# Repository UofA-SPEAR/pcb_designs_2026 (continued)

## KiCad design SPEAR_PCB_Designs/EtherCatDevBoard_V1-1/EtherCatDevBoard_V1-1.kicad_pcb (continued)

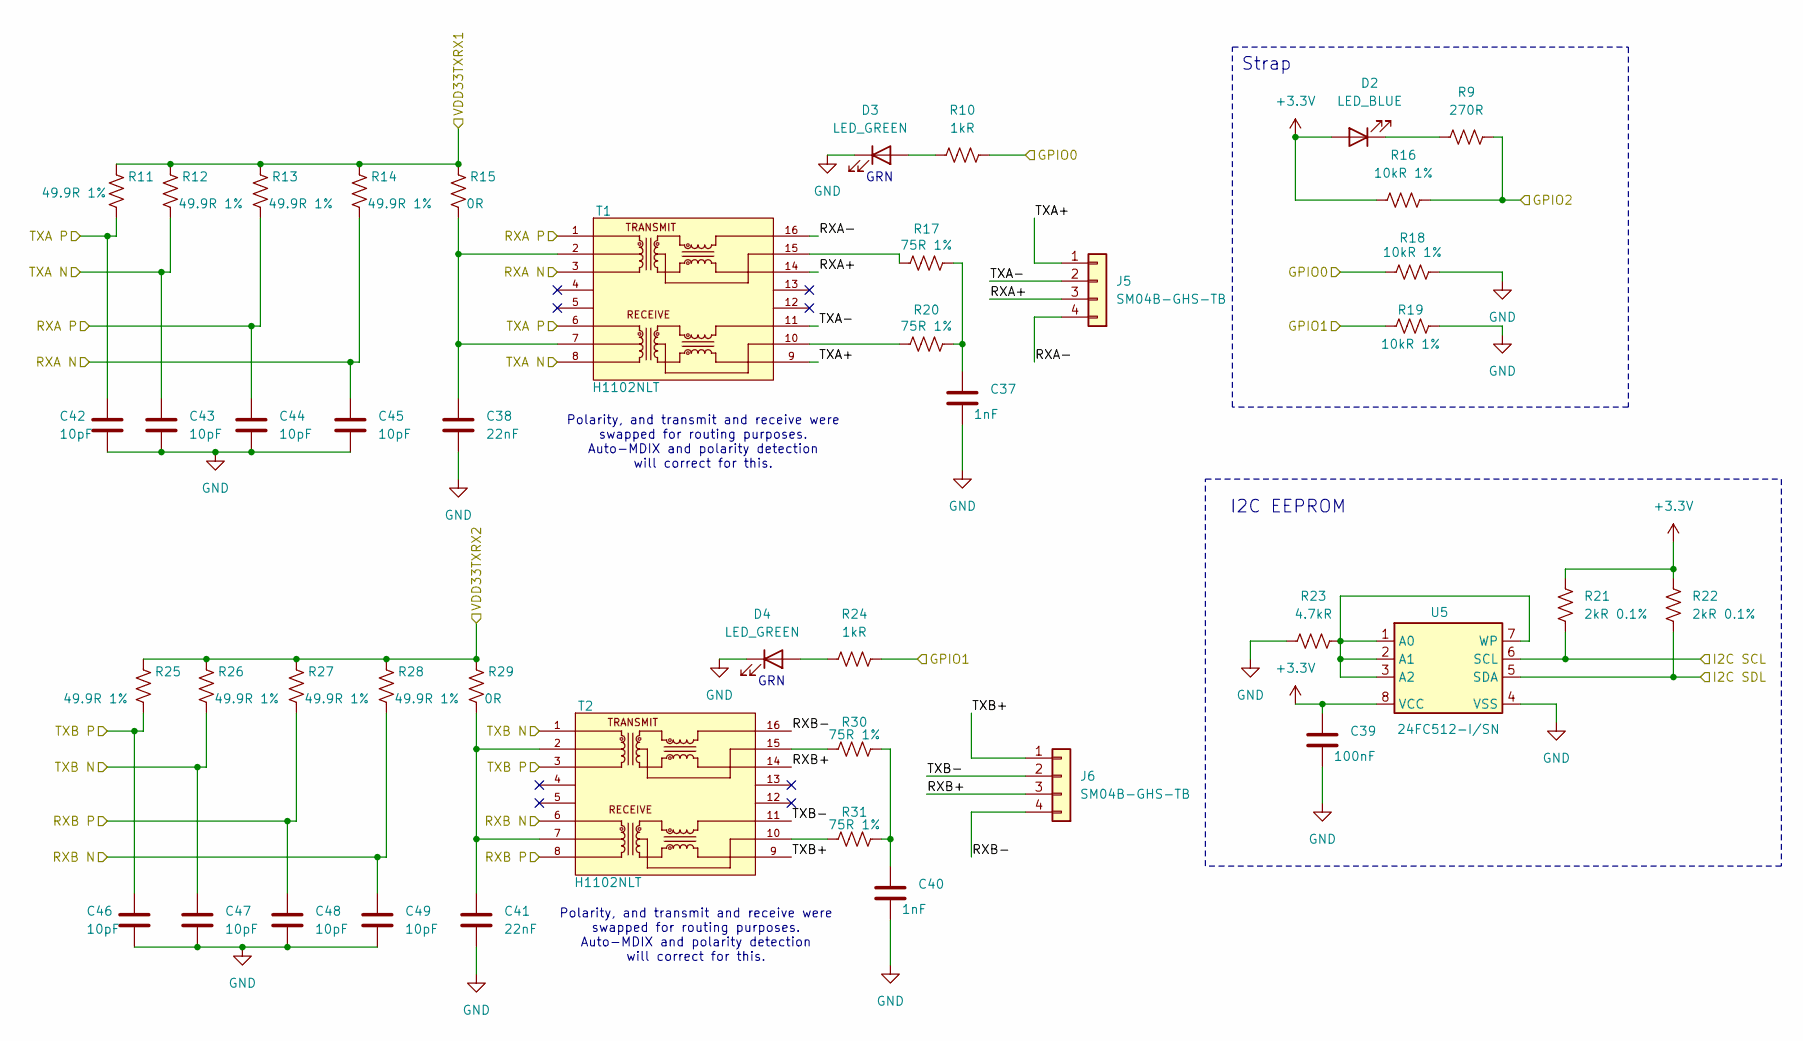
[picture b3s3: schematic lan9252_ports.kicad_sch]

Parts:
C37, C40: 1nF; C_0402_1005Metric; DigiKey_Part_Number 1276-1032-1-ND
C38, C41: 22nF; C_0402_1005Metric; DigiKey_Part_Number 1276-1537-1-ND
C39: 100nF; C_0402_1005Metric; DigiKey_Part_Number 1276-1043-1-ND
C42, C43, C44, C45, C46, C47, C48, C49: 10pF; C_0402_1005Metric; DigiKey_Part_Number 1276-1139-1-ND
D2: LED_BLUE; LED_0603_1608Metric; DigiKey_Part_Number 732-12013-1-ND
D3, D4: LED_GREEN; LED_0603_1608Metric; DigiKey_Part_Number 732-12017-1-ND
J5, J6: SM04B-GHS-TB; JST_GH_SM04B-GHS-TB_1x04-1MP_P1.25mm_Horizontal; DigiKey_Part_Number 455-1566-1-ND
R9: 270R; R_0402_1005Metric; DigiKey_Part_Number 311-270LRCT-ND
R10, R24: 1kR; R_0402_1005Metric; DigiKey_Part_Number 311-1.0KJRCT-ND
R11, R12, R13, R14, R25, R26, R27, R28: 49.9R 1%; R_0402_1005Metric; DigiKey_Part_Number 311-49.9LRCT-ND
R15, R29: 0R; R_0402_1005Metric; DigiKey_Part_Number 311-0.0JRCT-ND
R16, R18, R19: 10kR 1%; R_0402_1005Metric; DigiKey_Part_Number 311-10.0KLRCT-ND
R17, R20, R30, R31: 75R 1%; R_0402_1005Metric; DigiKey_Part_Number 13-RC0402FR-1375RLCT-ND
R21, R22: 2kR 0.1%; R_0402_1005Metric; DigiKey_Part_Number YAG2303CT-ND
R23: 4.7kR; R_0402_1005Metric; DigiKey_Part_Number 311-4.7KJRCT-ND
T1, T2: H1102NLT; XFMR_H1102NLT; PARTREV NA; DigiKey_Part_Number 553-1532-1-ND
U5: 24FC512-I/SN; SOIC-8_3.9x4.9mm_P1.27mm; DigiKey_Part_Number 24FC512-I/SN-ND

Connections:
+3.3V: C39.1, D2.2 (A), R16.2, R21.1, R22.1, U5.8 (VCC); also elsewhere on the board
/LAN9252/GPIO0: R10.1, R18.2; also elsewhere on the board
/LAN9252/GPIO1: R19.2, R24.1; also elsewhere on the board
/LAN9252/GPIO2: R9.1, R16.1; also elsewhere on the board
/LAN9252/I2C_SCL: R21.2, U5.6 (SCL); also elsewhere on the board
/LAN9252/I2C_SDL: R22.2, U5.5 (SDA); also elsewhere on the board
/LAN9252/LAN9252 Ports/RXA+: J5.3, T1.14
/LAN9252/LAN9252 Ports/RXA-: J5.4, T1.16
/LAN9252/LAN9252 Ports/RXB+: J6.3, T2.14
/LAN9252/LAN9252 Ports/RXB-: J6.4, T2.16
/LAN9252/LAN9252 Ports/TXA+: J5.1, T1.9
/LAN9252/LAN9252 Ports/TXA-: J5.2, T1.11
/LAN9252/LAN9252 Ports/TXB+: J6.1, T2.9
/LAN9252/LAN9252 Ports/TXB-: J6.2, T2.11
/LAN9252/RXA_N: C45.1, R14.2, T1.3; also elsewhere on the board
/LAN9252/RXA_P: C44.1, R13.2, T1.1; also elsewhere on the board
/LAN9252/RXB_N: C49.1, R28.2, T2.6; also elsewhere on the board
/LAN9252/RXB_P: C48.1, R27.2, T2.8; also elsewhere on the board
/LAN9252/TXA_N: C43.1, R12.2, T1.8; also elsewhere on the board
/LAN9252/TXA_P: C42.1, R11.2, T1.6; also elsewhere on the board
/LAN9252/TXB_N: C47.1, R26.2, T2.1; also elsewhere on the board
/LAN9252/TXB_P: C46.1, R25.2, T2.3; also elsewhere on the board
/LAN9252/VDD33TXRX1: R11.1, R12.1, R13.1, R14.1, R15.1; also elsewhere on the board
/LAN9252/VDD33TXRX2: R25.1, R26.1, R27.1, R28.1, R29.1; also elsewhere on the board
GND: C37.2, C38.2, C39.2, C40.2, C41.2, C42.2, C43.2, C44.2, C45.2, C46.2, C47.2, C48.2, C49.2, D3.1 (K), D4.1 (K), R18.1, R19.1, R23.1, U5.4 (VSS); also elsewhere on the board
unnamed: C37.1, R17.2, R20.2
unnamed: C38.1, R15.2, T1.2, T1.7
unnamed: C40.1, R30.2, R31.2
unnamed: C41.1, R29.2, T2.2, T2.7
unnamed: D2.1 (K), R9.2
unnamed: D3.2 (A), R10.2
unnamed: D4.2 (A), R24.2
unnamed: R17.1, T1.15
unnamed: R20.1, T1.10
unnamed: R30.1, T2.15
unnamed: R31.1, T2.10
unnamed: R23.2, U5.1 (A0), U5.2 (A1), U5.3 (A2), U5.7 (WP)

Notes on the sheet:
Polarity, and transmit and receive were swapped for routing purposes. Auto-MDIX and polarity detection will correct for this.
GRN
Strap
I2C EEPROM

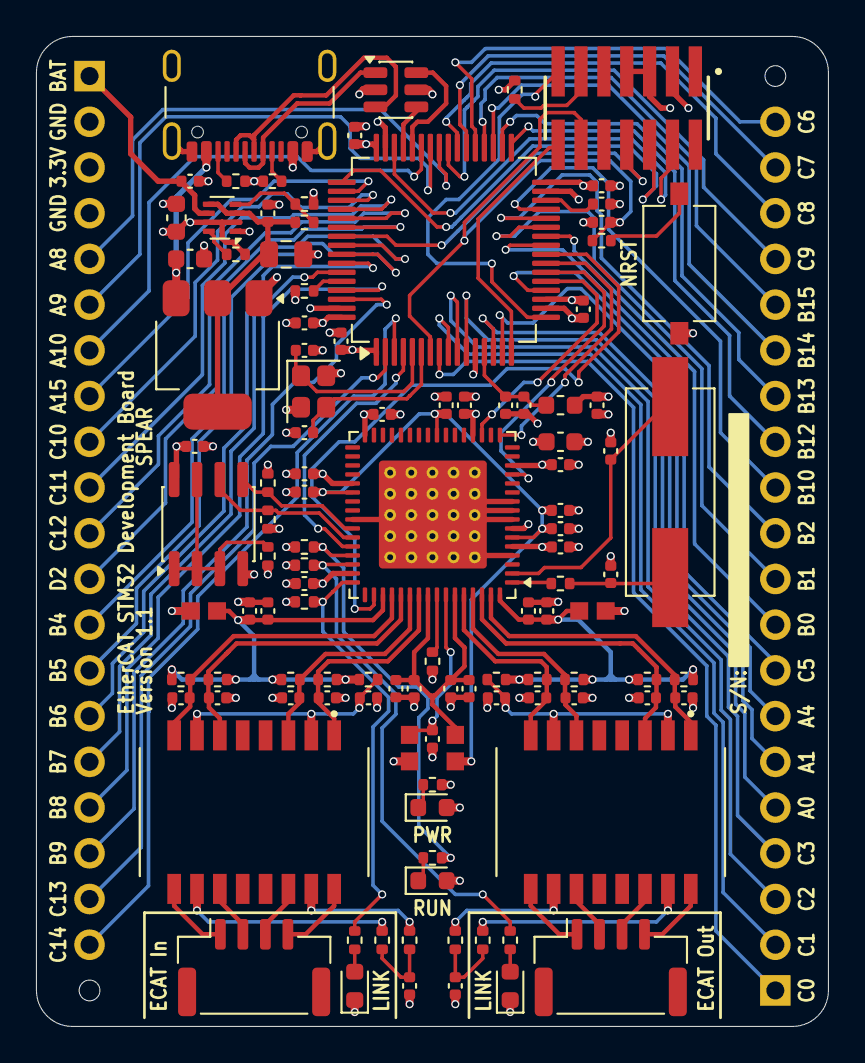
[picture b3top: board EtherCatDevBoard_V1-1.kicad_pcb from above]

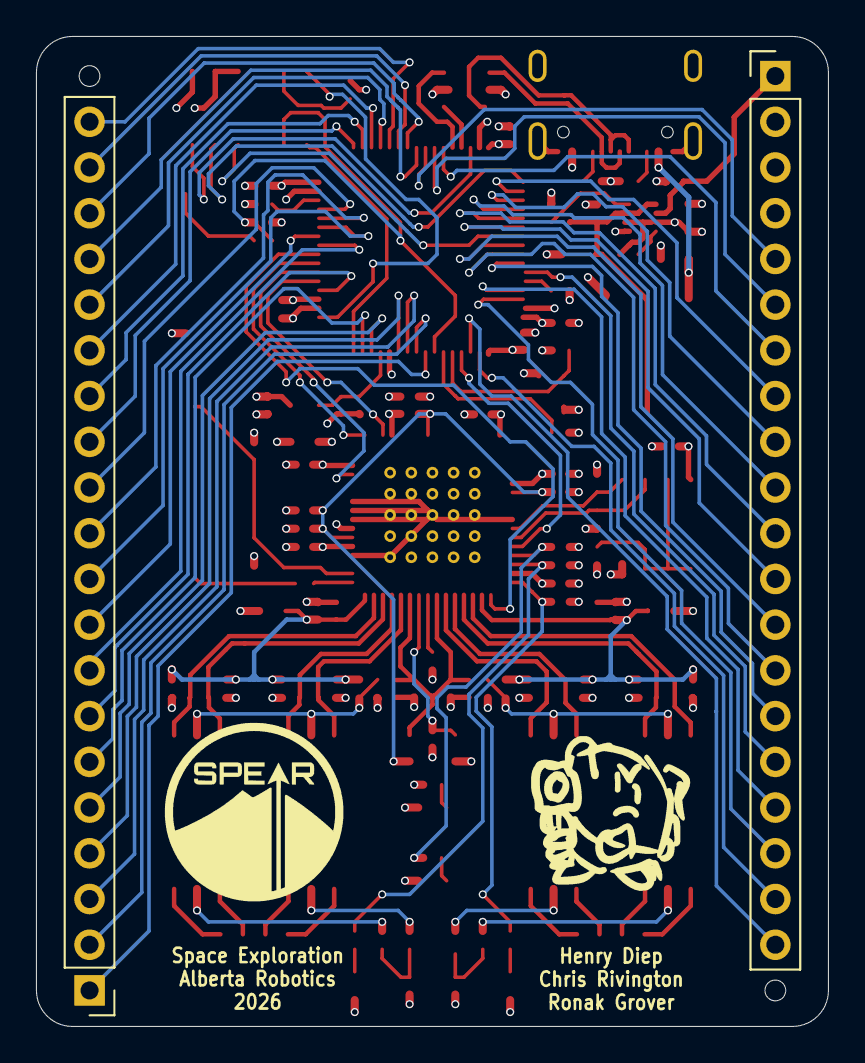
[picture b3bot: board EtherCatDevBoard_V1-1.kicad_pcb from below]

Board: 4 copper layers, 44.0 x 55.0 mm, 112 parts (2 on the bottom side), 110 nets.

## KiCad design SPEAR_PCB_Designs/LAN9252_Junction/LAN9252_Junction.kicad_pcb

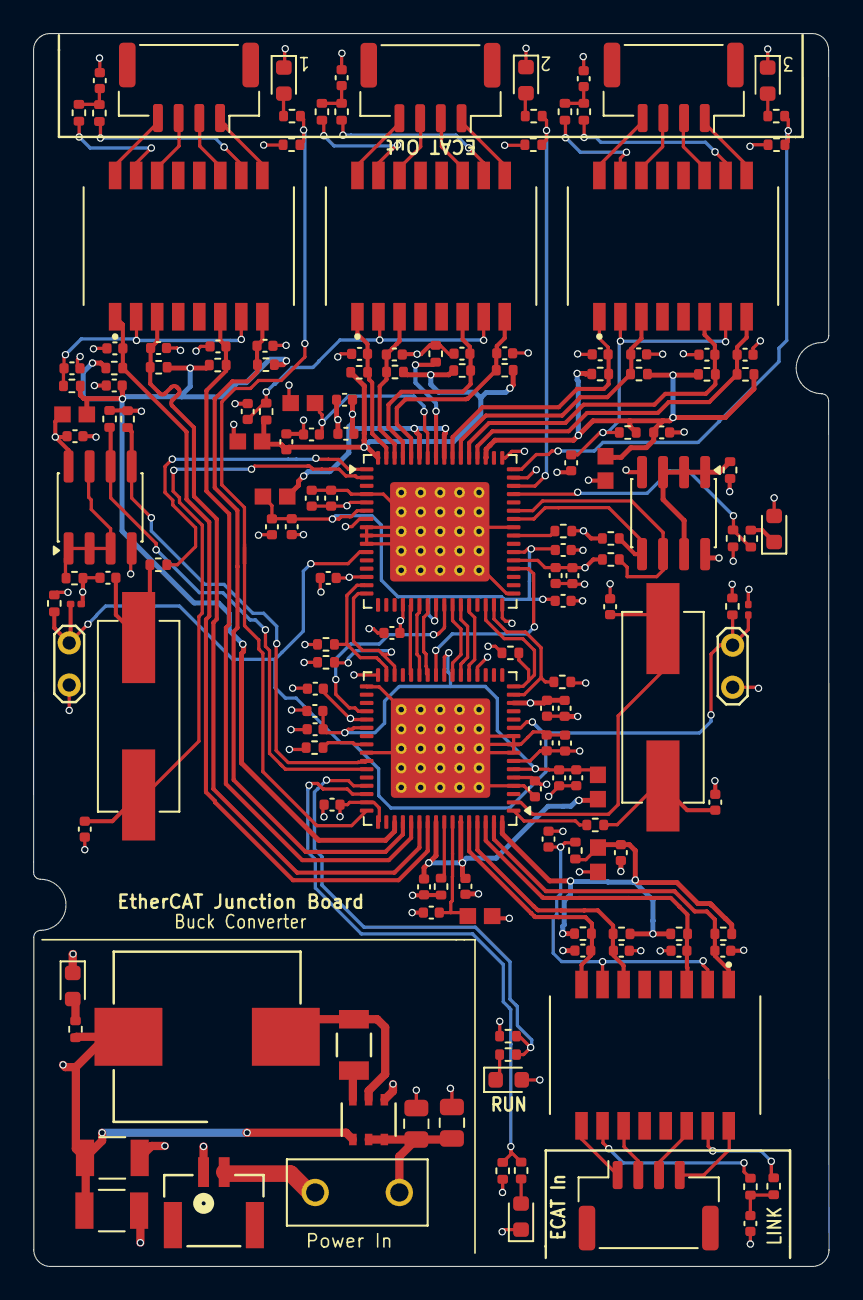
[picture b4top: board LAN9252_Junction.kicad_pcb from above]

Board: 4 copper layers, 48.0 x 74.4 mm, 161 parts (0 on the bottom side), 106 nets.

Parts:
C1, C4, C31, C34: 18pF; C_0402_1005Metric
C2, C3, C5, C6, C8, C9, C11, C12, C13, C14, C15, C16, C17, C32, C33, C35, C36, C38, C39, C41, C42, C43, C44, C45, C46, C47: 0.1uF; C_0402_1005Metric
C7, C37: 1uF; C_0402_1005Metric
C10, C40: 470 pF; C_0402_1005Metric
C18, C19, C20, C21, C22, C23, C24, C25, C48, C49, C50, C51, C52, C53, C54, C55: 10p; C_0402_1005Metric
C26, C27, C56, C57: 22n; C_0402_1005Metric
C28, C29, C58, C59: 1000 pF; C_0402_1005Metric
C30, C60: 0.1 uF; C_0402_1005Metric
C61, C62: 10uF; C_0805_2012Metric
C63: 150nF; CAP_CC1206_YAG
C64, C65: 22uF; CAP_C3225X7R1C226M250AC
C66, C67: 0.1uF; C_0201_0603Metric
D1, D2, D3, D4, D5, D6, D7: LED; LED_0603_1608Metric
F3: 2A; FUSE_36912000440
FB1, FB3, FB4, FB5, FB7, FB8: BLM18EG221SN1D; Ferrite_bead
FB2, FB6: FerriteBead; Ferrite_bead
J1, J2, J3, J4: SM04B-GHS-TB; JST_GH_SM04B-GHS-TB_1x04-1MP_P1.25mm_Horizontal
J5: SM02B-GHS-TB; CONN_SM02B-GHS_JST
J8, J9: Conn_01x02_Pin; TestPoint_2Pads_Pitch2.54mm_Drill0.8mm
L1: 3.9uH; L_Wurth_WE-LHMI-1040_L1
R1, R2: 4K7; R_0402_1005Metric
R3, R15, R16, R30, R42, R43: 0R; R_0402_1005Metric
R4, R31: 12.1k; R_0402_1005Metric
R5, R6, R32, R33: 141 R; R_0402_1005Metric
R7, R8, R9, R10, R11, R12, R13, R14, R34, R35, R36, R37, R38, R39, R40, R41: 49.9R 1%; R_0402_1005Metric
R17, R22, R44, R49, R59: 1k; R_0402_1005Metric
R18, R19, R20, R21, R45, R46, R47, R48: 75R 1%; R_0402_1005Metric
R23, R50: 4.7kR; R_0402_1005Metric
R24, R25, R26, R51, R52, R53: 10kR; R_0402_1005Metric
R27, R54: 270R; R_0402_1005Metric
R28, R29, R55, R56: 2kR; R_0402_1005Metric
R57, R58: 10k; R_0402_1005Metric
T1, T2, T3, T4: H1102NLT; XFMR_H1102NLT
U1, U3: LAN9252_ML; LAN9252_QFN UPDATED
U2, U4: 24FC512; SOIC-8_3.9x4.9mm_P1.27mm
U5: AP63203WU; AP63203WU-7_DIO-L
Y1, Y2: 25MHz; Y_Wurth_WE-XTAL_Quartz-HC49-4HSMX

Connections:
+3.3V: C11.1, C13.1, C14.1, C15.1, C16.1, C17.1, C30.1, C41.1, C43.1, C44.1, C45.1, C46.1, C47.1, C60.1, C64.1, C65.1, D3.2 (A), D6.2 (A), FB1.1, FB2.1, FB3.2, FB5.1, FB6.1, FB7.2, L1.2, R1.2, R2.2, R24.2, R26.1, R28.1, R29.1, R51.2, R52.1, R53.1, R55.1, R56.1, R57.1, R58.1, R59.1, U1.5 (VDD33), U1.7 (REG_EN), U1.14 (VDDIO), U1.20 (VDDIO__1), U1.32 (VDDIO__2), U1.37 (VDDIO__3), U1.47 (VDDIO__4), U1.49 (D4/GPI3/GPO3), U2.8 (VCC), U3.5 (VDD33), U3.7 (REG_EN), U3.14 (VDDIO), U3.20 (VDDIO__1), U3.32 (VDDIO__2), U3.37 (VDDIO__3), U3.47 (VDDIO__4), U3.49 (D4/GPI3/GPO3), U4.8 (VCC), U5.1 (FB)
/Buck Converter/BST: C63.2, U5.6 (BST)
/Buck Converter/BUCK_PWR: C61.1, C62.1, F3.1, U5.2 (EN), U5.3 (IN)
/Buck Converter/SW: C63.1, L1.1, U5.5 (SW)
/LAN9252 System 1/GPIO0: R22.1, R25.2, U1.48 (LINKACTLED0/TDO/~CHIP_MODE0)
/LAN9252 System 1/GPIO1: R17.1, R26.2, U1.46 (LINKACTLED1/TDI/~CHIP_MODE1)
/LAN9252 System 1/GPIO2: R24.1, R27.1, U1.45 (RUNLED/~E2PSIZE)
/LAN9252 System 1/I2C_SCL: R28.2, U1.43 (EESCL/TCK), U2.6 (SCL)
/LAN9252 System 1/I2C_SDL: R29.2, U1.42 (EESDA/TMS), U2.5 (SDA)
/LAN9252 System 1/LAN9252 Ports/RXA+: J2.3, T2.14
/LAN9252 System 1/LAN9252 Ports/RXA-: J2.4, T2.16
/LAN9252 System 1/LAN9252 Ports/RXB+: J1.3, T1.14
/LAN9252 System 1/LAN9252 Ports/RXB-: J1.4, T1.16
/LAN9252 System 1/LAN9252 Ports/TXA+: J2.1, T2.9
/LAN9252 System 1/LAN9252 Ports/TXA-: J2.2, T2.11
/LAN9252 System 1/LAN9252 Ports/TXB+: J1.1, T1.9
/LAN9252 System 1/LAN9252 Ports/TXB-: J1.2, T1.11
/LAN9252 System 1/MII_CLK25: U1.25 (A1/ALELO), U3.36 (D6/GPI0/GPO0)
/LAN9252 System 1/MII_MDIO: R1.1, U1.40 (D8/GPI2/GPO2)
/LAN9252 System 1/MII_RXCLK: U1.36 (D6/GPI0/GPO0), U3.25 (A1/ALELO)
/LAN9252 System 1/MII_RXD0: U1.27 (A4/GPI12/GPO12), U3.22 (D11/GPI5/GPO5)
/LAN9252 System 1/MII_RXD1: U1.28 (CS/GPI13/GPO13), U3.21 (D12/GPI6/GPO6)
/LAN9252 System 1/MII_RXD2: R32.1, U1.30 (WR/GPI14/GPO14), U3.16 (D13/GPI7/GPO7/~TX_SHIFT0)
/LAN9252 System 1/MII_RXD3: R33.1, U1.31 (RD/GPI15/GPO15), U3.15 (D14/GPI8/GPO8/~TX_SHIFT1)
/LAN9252 System 1/MII_RXDV: U1.26 (A3/GPI11/GPO11), U3.23 (D10/GPI4/GPO4)
/LAN9252 System 1/MII_TXD0: U1.22 (D11/GPI5/GPO5), U3.27 (A4/GPI12/GPO12)
/LAN9252 System 1/MII_TXD1: U1.21 (D12/GPI6/GPO6), U3.28 (CS/GPI13/GPO13)
/LAN9252 System 1/MII_TXD2: R5.1, U1.16 (D13/GPI7/GPO7/~TX_SHIFT0), U3.30 (WR/GPI14/GPO14)
/LAN9252 System 1/MII_TXD3: R6.1, U1.15 (D14/GPI8/GPO8/~TX_SHIFT1), U3.31 (RD/GPI15/GPO15)
/LAN9252 System 1/MII_TXEN: U1.23 (D10/GPI4/GPO4), U3.26 (A3/GPI11/GPO11)
/LAN9252 System 1/RST: C66.1, C67.1, J8.1, J9.1, R57.2, R58.2, U1.11 (~RST), U3.11 (~RST)
/LAN9252 System 1/RXA_N: C24.1, R13.2, T2.3, U1.54 (RXNA)
/LAN9252 System 1/RXA_P: C22.1, R11.2, T2.1, U1.55 (RXPA)
/LAN9252 System 1/RXB_N: C25.1, R14.2, T1.6, U1.61 (RXNB)
/LAN9252 System 1/RXB_P: C23.1, R12.2, T1.8, U1.60 (RXPB)
/LAN9252 System 1/TXA_N: C20.1, R9.2, T2.8, U1.52 (TXNA)
/LAN9252 System 1/TXA_P: C18.1, R7.2, T2.6, U1.53 (TXPA)
/LAN9252 System 1/TXB_N: C21.1, R10.2, T1.1, U1.63 (TXNB)
/LAN9252 System 1/TXB_P: C19.1, R8.2, T1.3, U1.62 (TXPB)
/LAN9252 System 1/VDD12TX1: C6.1, C8.1, FB4.1, U1.56 (VDD12TX1), U1.59 (VDD12TX2)
/LAN9252 System 1/VDD33TXRX1: C2.1, FB1.2, R7.1, R9.1, R11.1, R13.1, R15.1, U1.51 (VDD33TXRX1)
/LAN9252 System 1/VDD33TXRX2: C3.1, FB2.2, R8.1, R10.1, R12.1, R14.1, R16.1, U1.64 (VDD33TXRX2)
/LAN9252 System 1/VDDCR: C7.1, C9.1, C10.1, C12.1, FB4.2, U1.6 (VDDCR), U1.24 (VDDCR__1), U1.38 (VDDCR__2)
/LAN9252 System 2/GPIO0: R49.1, R52.2, U3.48 (LINKACTLED0/TDO/~CHIP_MODE0)
/LAN9252 System 2/GPIO1: R44.1, R53.2, U3.46 (LINKACTLED1/TDI/~CHIP_MODE1)
/LAN9252 System 2/GPIO2: R51.1, R54.1, U3.45 (RUNLED/~E2PSIZE)
/LAN9252 System 2/I2C_SCL: R55.2, U3.43 (EESCL/TCK), U4.6 (SCL)
/LAN9252 System 2/I2C_SDL: R56.2, U3.42 (EESDA/TMS), U4.5 (SDA)
/LAN9252 System 2/LAN9252 Ports/RXA+: J4.3, T4.14
/LAN9252 System 2/LAN9252 Ports/RXA-: J4.4, T4.16
/LAN9252 System 2/LAN9252 Ports/RXB+: J3.3, T3.14
/LAN9252 System 2/LAN9252 Ports/RXB-: J3.4, T3.16
/LAN9252 System 2/LAN9252 Ports/TXA+: J4.1, T4.9
/LAN9252 System 2/LAN9252 Ports/TXA-: J4.2, T4.11
/LAN9252 System 2/LAN9252 Ports/TXB+: J3.1, T3.9
/LAN9252 System 2/LAN9252 Ports/TXB-: J3.2, T3.11
/LAN9252 System 2/MII_MDIO: R2.1, U3.40 (D8/GPI2/GPO2)
/LAN9252 System 2/RXA_N: C54.1, R40.2, T4.3, U3.54 (RXNA)
/LAN9252 System 2/RXA_P: C52.1, R38.2, T4.1, U3.55 (RXPA)
/LAN9252 System 2/RXB_N: C55.1, R41.2, T3.6, U3.61 (RXNB)
/LAN9252 System 2/RXB_P: C53.1, R39.2, T3.8, U3.60 (RXPB)
/LAN9252 System 2/TXA_N: C50.1, R36.2, T4.8, U3.52 (TXNA)
/LAN9252 System 2/TXA_P: C48.1, R34.2, T4.6, U3.53 (TXPA)
/LAN9252 System 2/TXB_N: C51.1, R37.2, T3.1, U3.63 (TXNB)
/LAN9252 System 2/TXB_P: C49.1, R35.2, T3.3, U3.62 (TXPB)
/LAN9252 System 2/VDD12TX1: C36.1, C38.1, FB8.1, U3.56 (VDD12TX1), U3.59 (VDD12TX2)
/LAN9252 System 2/VDD33TXRX1: C32.1, FB5.2, R34.1, R36.1, R38.1, R40.1, R42.1, U3.51 (VDD33TXRX1)
/LAN9252 System 2/VDD33TXRX2: C33.1, FB6.2, R35.1, R37.1, R39.1, R41.1, R43.1, U3.64 (VDD33TXRX2)
/LAN9252 System 2/VDDCR: C37.1, C39.1, C40.1, C42.1, FB8.2, U3.6 (VDDCR), U3.24 (VDDCR__1), U3.38 (VDDCR__2)
GND: C1.1, C2.2, C3.2, C4.1, C5.2, C6.2, C7.2, C8.2, C9.2, C10.2, C11.2, C12.2, C13.2, C14.2, C15.2, C16.2, C17.2, C18.2, C19.2, C20.2, C21.2, C22.2, C23.2, C24.2, C25.2, C26.2, C27.2, C28.2, C29.2, C30.2, C31.1, C32.2, C33.2, C34.1, C35.2, C36.2, C37.2, C38.2, C39.2, C40.2, C41.2, C42.2, C43.2, C44.2, C45.2, C46.2, C47.2, C48.2, C49.2, C50.2, C51.2, C52.2, C53.2, C54.2, C55.2, C56.2, C57.2, C58.2, C59.2, C60.2, C61.2, C62.2, C64.2, C65.2, C66.2, C67.2, D1.1 (K), D2.1 (K), D4.1 (K), D5.1 (K), D7.1 (K), J5.1, J8.2, J9.2, R4.1, R5.2, R6.2, R23.1, R25.1, R31.1, R32.2, R33.2, R50.1, U1.4 (OSCVSS), U1.8 (~FXLOSEN), U1.9 (FXSDA/FXLOSA/~FXSDENA), U1.10 (FXSDB/FXLOSB/~FXSDENB), U1.33 (A0/D15/GPI9/GPO9), U1.41 (TESTMODE), U1.65 (VSS), U2.4 (VSS), U3.4 (OSCVSS), U3.8 (~FXLOSEN), U3.9 (FXSDA/FXLOSA/~FXSDENA), U3.10 (FXSDB/FXLOSB/~FXSDENB), U3.33 (A0/D15/GPI9/GPO9), U3.41 (TESTMODE), U3.65 (VSS), U4.4 (VSS), U5.4 (GND)
unnamed: C1.2, R3.1, Y1.2
unnamed: C26.1, R15.2, T2.2, T2.7
unnamed: C27.1, R16.2, T1.2, T1.7
unnamed: C28.1, R18.2, R19.2
unnamed: C29.1, R20.2, R21.2
unnamed: C31.2, R30.1, Y2.2
unnamed: C56.1, R42.2, T4.2, T4.7
unnamed: C57.1, R43.2, T3.2, T3.7
unnamed: C58.1, R45.2, R46.2
unnamed: C59.1, R47.2, R48.2
unnamed: D1.2 (A), R17.2
unnamed: D2.2 (A), R22.2
unnamed: D3.1 (K), R27.2
unnamed: D4.2 (A), R44.2
unnamed: D5.2 (A), R49.2
unnamed: D6.1 (K), R54.2
unnamed: D7.2 (A), R59.2
unnamed: F3.2, J5.2
unnamed: R18.1, T1.15
unnamed: R19.1, T1.10
unnamed: R20.1, T2.15
unnamed: R21.1, T2.10
unnamed: R45.1, T3.15
unnamed: R46.1, T3.10
unnamed: R47.1, T4.15
unnamed: R48.1, T4.10
unnamed: R3.2, U1.1 (OSCI)
unnamed: C4.2, U1.2 (OSCO), Y1.1
unnamed: R4.2, U1.57 (RBIAS)
unnamed: C5.1, FB3.1, U1.58 (VDD33BIAS)
unnamed: R23.2, U2.1 (A0), U2.2 (A1), U2.3 (A2), U2.7 (WP)
unnamed: R30.2, U3.1 (OSCI)
unnamed: C34.2, U3.2 (OSCO), Y2.1
unnamed: R31.2, U3.57 (RBIAS)
unnamed: C35.1, FB7.1, U3.58 (VDD33BIAS)
unnamed: R50.2, U4.1 (A0), U4.2 (A1), U4.3 (A2), U4.7 (WP)

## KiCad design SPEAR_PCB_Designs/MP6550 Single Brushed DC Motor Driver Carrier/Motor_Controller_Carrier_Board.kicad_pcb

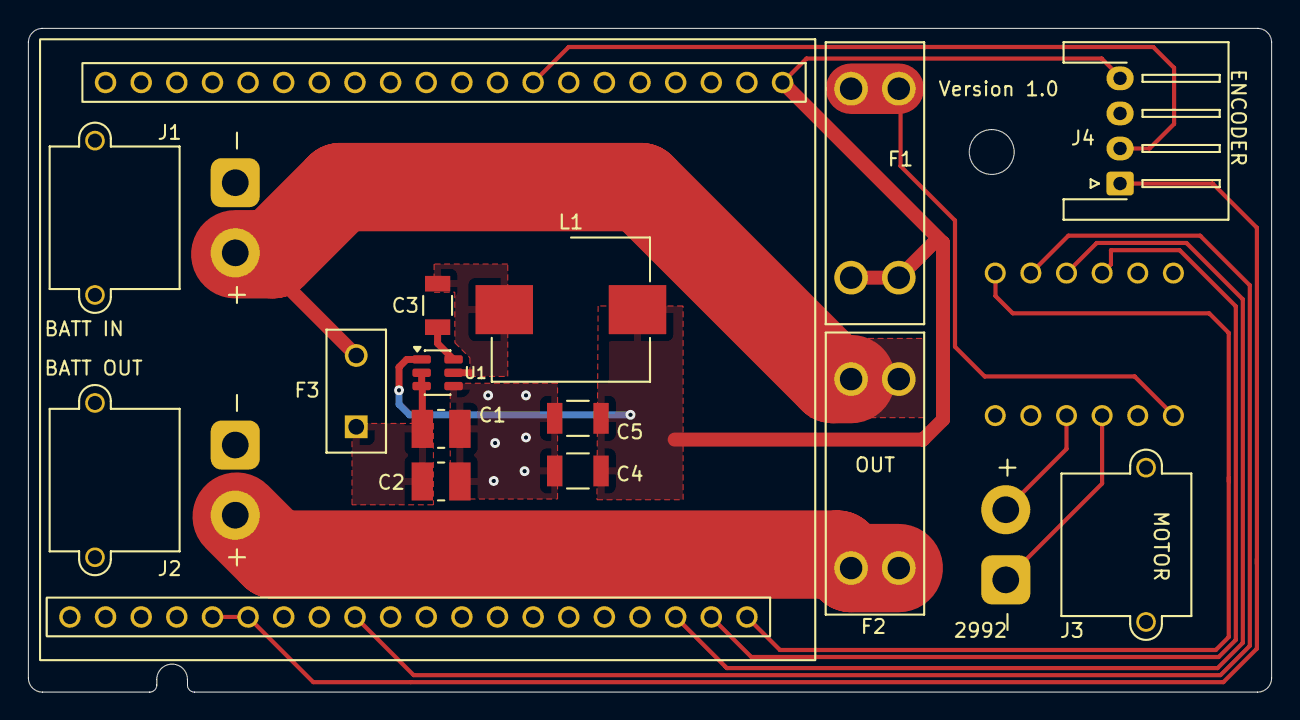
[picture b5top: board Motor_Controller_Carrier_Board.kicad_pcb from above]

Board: 2 copper layers, 88.6 x 47.3 mm, 16 parts (0 on the bottom side), 16 nets.

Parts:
C1, C2: 10uF; CAPC3225X270N
C3: 150nF; CAP_CC1206_YAG
C4, C5: 22uF; CAP_C3225X7R1C226M250AC
F1: 2A; FUSE_3557-10
F2: 15A; FUSE_3557-15
F3: 2A; FUS_LITTELFUSE_392_LTF
J1, J2, J3: Conn_01x02_Pin; AMASS_XT30PW-M_1x02_P2.50mm_Horizontal_1
J4: Conn_01x04_Pin; JST_XH_S4B-XH-A-1_1x04_P2.50mm_Horizontal
L1: 3.9uH; L_Wurth_WE-LHMI-1040_L1
MCB1: Micro_Controller_Board
MDB3: Motor_Driver_Board_4733
U1: AP63203WU; TSOT-23-6

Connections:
+3.3V: C4.1, C5.1, F1.1_1, F1.1_2, J4.4, L1.2, MCB1.1 (3.3V_Battery), U1.1 (FB)
/Schematic/ADC: MCB1.32 (PB0), MDB3.5 (VISEN)
/Schematic/BST: C3.2, U1.6 (BST)
/Schematic/BUCK_PWR: C1.1, C2.1, F3.1, U1.2 (EN), U1.3 (IN)
/Schematic/ENC_A: J4.2, MCB1.8 (PA15)
/Schematic/ENC_B: J4.1, MCB1.35 (PA1), MCB1.36 (PA0)
/Schematic/GPIO: MCB1.21 (PC6), MDB3.6 (SLEEP)
/Schematic/PWM1: MCB1.22 (PC7), MDB3.3 (IN2)
/Schematic/PWM2: MCB1.23 (PC8), MDB3.4 (IN1)
/Schematic/SW: C3.1, L1.1, U1.5 (SW)
GND: C1.2, C2.2, C4.2, C5.2, J1.1, J2.1, J4.3, MCB1.2 (GND), MCB1.4 (GND), MDB3.2 (GND), MDB3.8 (GND), MDB3.11 (ISET), MDB3.12 (V3P3), U1.4 (GND)
unnamed: F2.1_1, F2.1_2, F3.2, J1.2
unnamed: F2.2_1, F2.2_2, J2.2
unnamed: J3.1, MDB3.9 (OUT2)
unnamed: J3.2, MDB3.10 (OUT1)
unnamed: F1.2_1, F1.2_2, MDB3.7 (VIN)

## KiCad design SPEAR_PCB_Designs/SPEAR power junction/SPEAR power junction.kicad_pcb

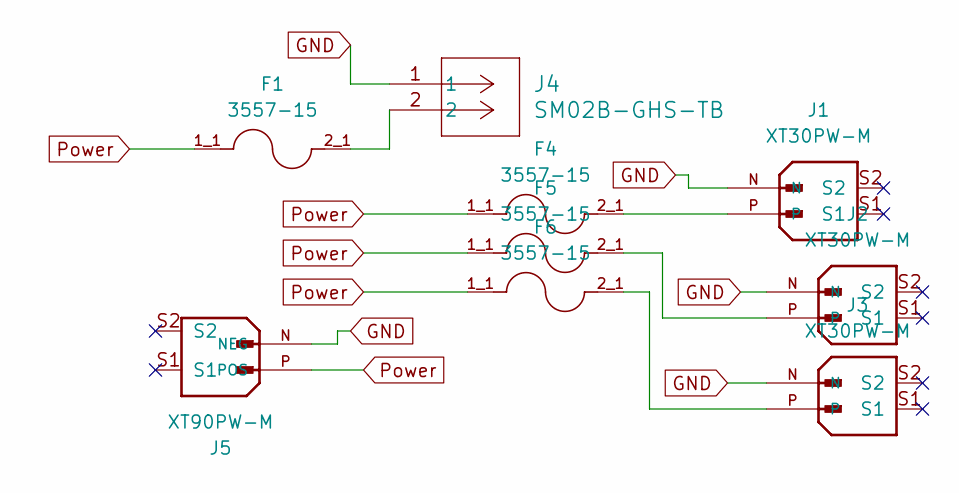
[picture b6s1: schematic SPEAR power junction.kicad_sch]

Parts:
F1, F4, F5, F6: 3557-15; FUSE_3557-15; PARTREV D
J1, J2, J3: XT30PW-M; AMASS_XT30PW-M; PARTREV 1.2
J4: SM02B-GHS-TB; CONN_SM02B-GHS_JST
J5: XT90PW-M; AMASS_XT90PW-M; PARTREV V00

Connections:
GND: J1.N, J2.N, J3.N, J4.1, J5.N (NEG)
unnamed: F1.2_1, F1.2_2, J4.2
unnamed: F4.2_1, F4.2_2, J1.P
unnamed: F5.2_1, F5.2_2, J2.P
unnamed: F6.2_1, F6.2_2, J3.P
Power: F1.1_1, F1.1_2, F4.1_1, F4.1_2, F5.1_1, F5.1_2, F6.1_1, F6.1_2, J5.P (POS)

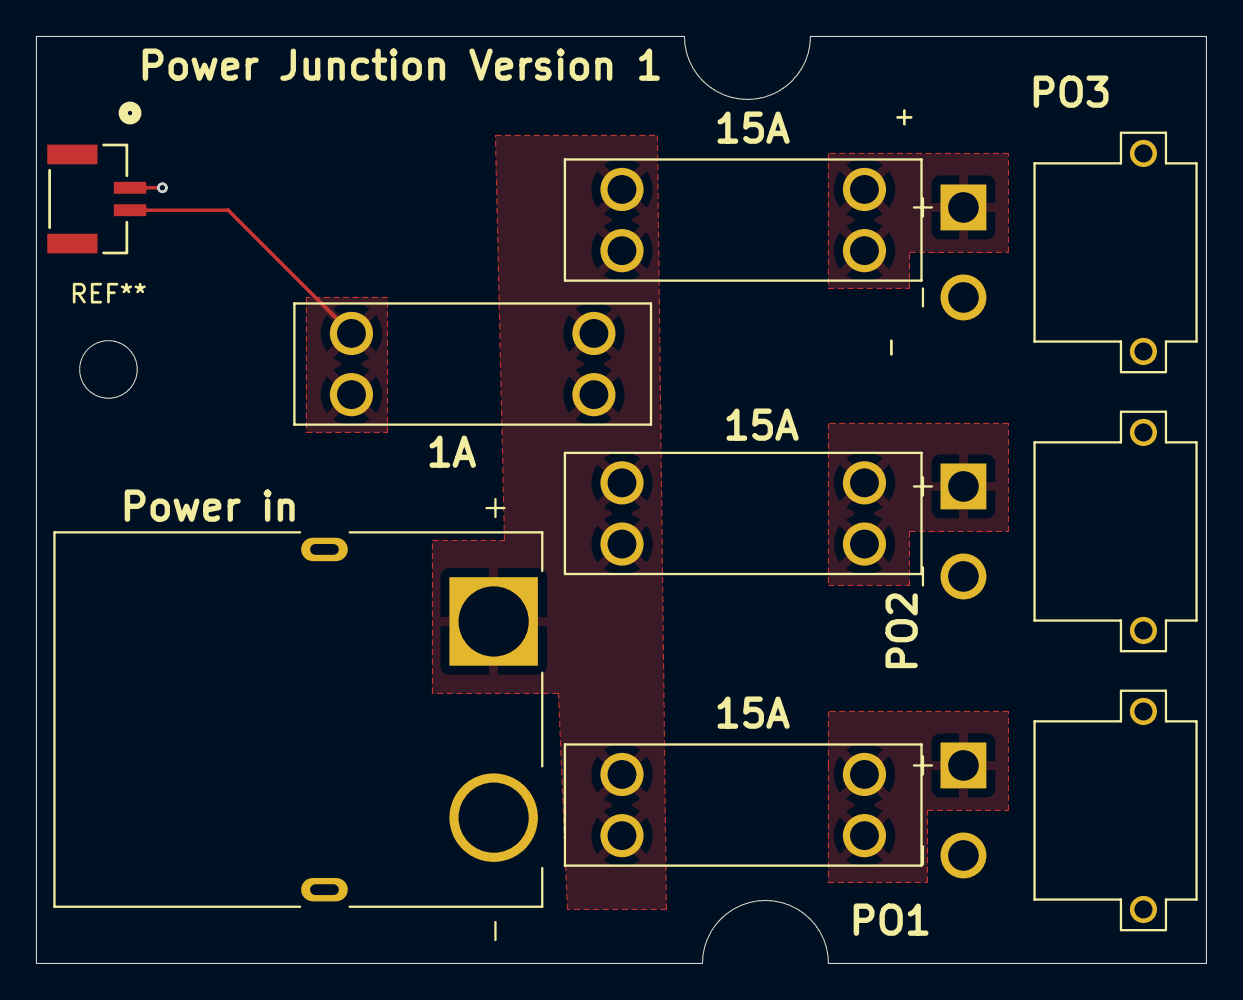
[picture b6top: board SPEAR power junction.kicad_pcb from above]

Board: 2 copper layers, 65.0 x 51.5 mm, 9 parts (0 on the bottom side), 6 nets.

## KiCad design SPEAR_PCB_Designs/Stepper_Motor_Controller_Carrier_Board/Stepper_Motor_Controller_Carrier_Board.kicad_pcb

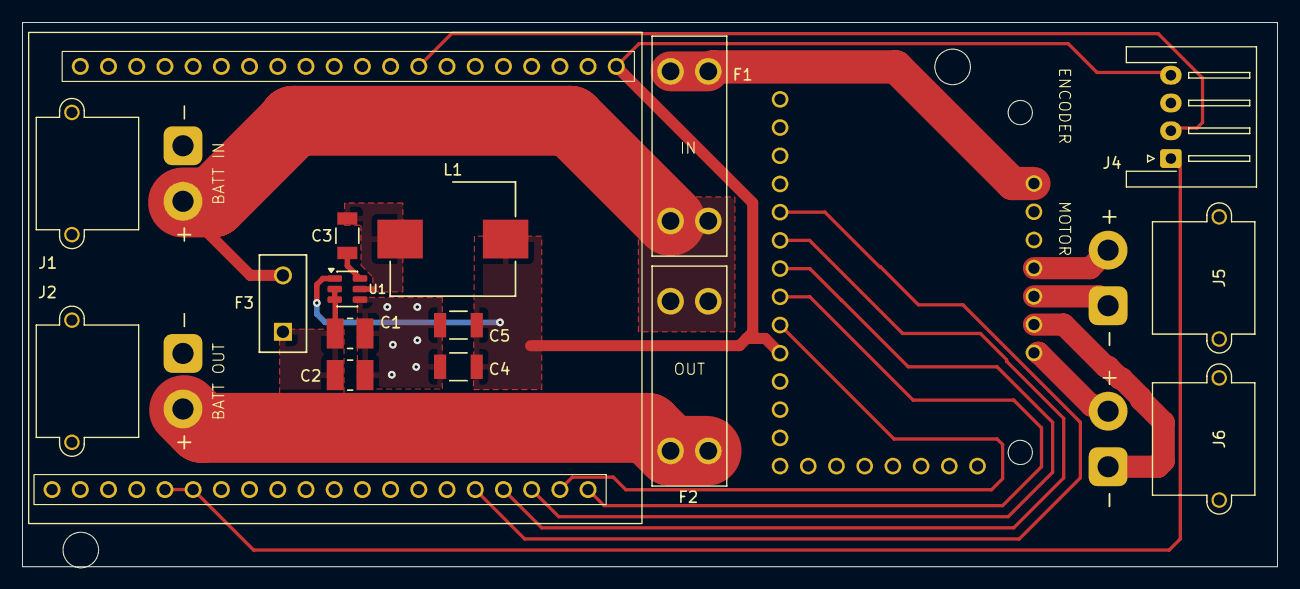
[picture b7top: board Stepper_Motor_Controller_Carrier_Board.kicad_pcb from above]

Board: 2 copper layers, 113.0 x 49.0 mm, 17 parts (0 on the bottom side), 19 nets.

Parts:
C1, C2: 10uF; CAPC3225X270N
C3: 150nF; CAP_CC1206_YAG
C4, C5: 22uF; CAP_C3225X7R1C226M250AC
F1: 3557-10; FUSE_3557-10
F2: 3557-15; FUSE_3557-15
F3: 2A; FUS_LITTELFUSE_392_LTF
J1, J2, J5, J6: Conn_01x02_Pin; AMASS_XT30PW-M_1x02_P2.50mm_Horizontal
J4: JST_S4B-XH-A-1; JST_XH_S4B-XH-A-1_1x04_P2.50mm_Horizontal
L1: 3.9uH; L_Wurth_WE-LHMI-1040_L1
MCB1: Micro_Controller_Board
MDB2: Motor_Driver_Board_2973
U1: AP63203WU; TSOT-23-6

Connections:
+3.3V: C4.1, C5.1, J4.4 (VCC), L1.2, MCB1.1 (3.3V_Battery), MDB2.10 (ENABLE), U1.1 (FB)
/CLK: MCB1.22 (PC7), MDB2.9 (STEP)
/DIR: MCB1.21 (PC6), MDB2.8 (DIR)
/DMODE0: MCB1.25 (PB15), MDB2.5 (DMODE0)
/DMODE1: MCB1.24 (PC9), MDB2.6 (DMODE1)
/DMODE2: MCB1.23 (PC8), MDB2.7 (DMODE2)
/DRIVER_PWR: F1.2_1, F1.2_2, MDB2.22 (VIN)
/ENC_A: J4.2 (A), MCB1.8 (PA15)
/ENC_B: J4.1 (B), MCB1.35 (PA1), MCB1.36 (PA0)
/Schematic/BST: C3.2, U1.6 (BST)
/Schematic/BUCK_PWR: C1.1, C2.1, F3.1, U1.2 (EN), U1.3 (IN)
/Schematic/SW: C3.1, L1.1, U1.5 (SW)
GND: C1.2, C2.2, C4.2, C5.2, J1.1, J2.1, J4.3 (GND), MCB1.2 (GND), MCB1.4 (GND), MDB2.2 (GND), MDB2.23 (GND), MDB2.24 (GND), U1.4 (GND)
unnamed: F1.1_1, F1.1_2, F2.1_1, F2.1_2, F3.2, J1.2
unnamed: F2.2_1, F2.2_2, J2.2
unnamed: J5.1, MDB2.26 (OUTB-)
unnamed: J5.2, MDB2.25 (OUTB+)
unnamed: J6.1, MDB2.27 (OUTA-)
unnamed: J6.2, MDB2.28 (OUTA+)

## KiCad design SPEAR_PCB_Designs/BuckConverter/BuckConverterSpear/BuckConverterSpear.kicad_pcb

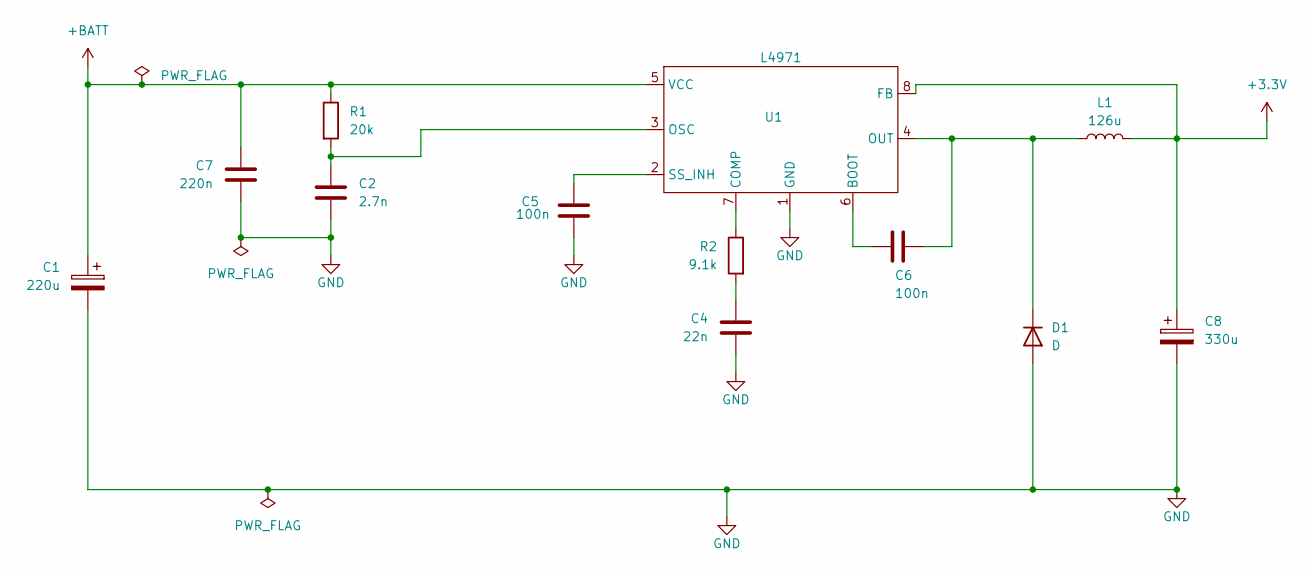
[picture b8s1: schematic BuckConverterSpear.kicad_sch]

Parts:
C1: 220u; CAP_021ASM_10X30_VIS_220u
C2: 2.7n; C_Disc_D5.0mm_W2.5mm_P2.50mm
C4: 22n; CAP_C321C_MOLDED RADIAL_KEM_C4_22n
C5, C6: 100n; C_Disc_D5.0mm_W2.5mm_P5.00mm
C7: 220n; CAP_C330_MR_COG_KEM_C7_220n
C8: 330u; CAP_RN_10X12P5_NCH_C8_330uF
D1: D; DO-15_STM_Diode
L1: 126u; L_Wurth_WE-SI_744114_126uH
R1: 20k; STA_CF14_STP_R1_20k
R2: 9.1k; STA_CF14_STP_R2_9.1k
U1: L4971; STM_L4P71

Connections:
+3.3V: C8.1, L1.2, U1.8 (FB)
+BATT: C1.1, C7.1, R1.1, U1.5 (VCC)
GND: C1.2, C2.2, C4.2, C5.2, C7.2, C8.2, D1.2 (A), U1.1 (GND)
unnamed: C4.1, R2.2
unnamed: C6.2, D1.1 (K), L1.1, U1.4 (OUT)
unnamed: C6.1, U1.6 (BOOT)
unnamed: R2.1, U1.7 (COMP)
unnamed: C2.1, R1.2, U1.3 (OSC)
unnamed: C5.1, U1.2 (SS_INH)

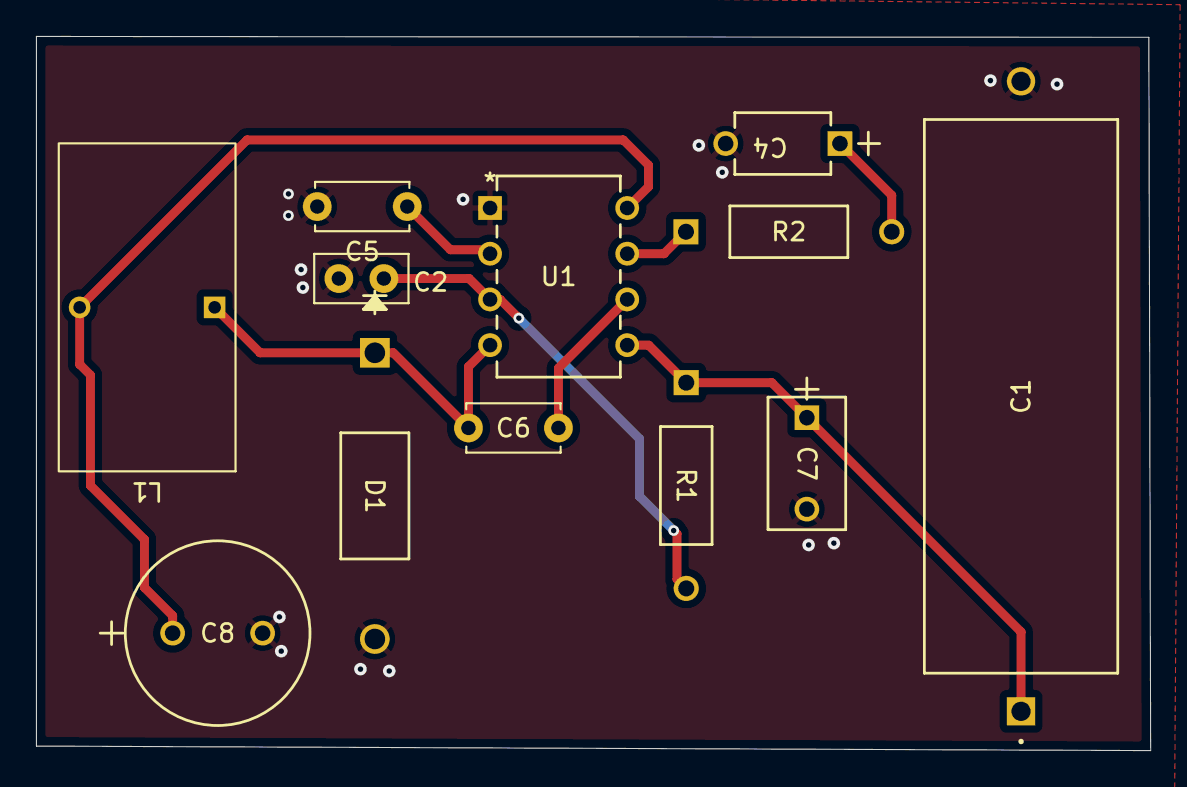
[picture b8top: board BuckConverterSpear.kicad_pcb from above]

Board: 2 copper layers, 61.9 x 39.7 mm, 12 parts (0 on the bottom side), 9 nets.

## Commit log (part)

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2025-11-02 Added footprint and symbol folders for SPEAR made footprints and symbols.
2025-11-02 Fixed spelling mistake of readme file name.
2025-11-02 Added XT30 Footprint
2025-11-08 Added a schematic and footprints for the LAN9252 board
2025-11-08 Added Motor Controller Carrier Board
2025-11-08 Made footprint for motor driver board
2025-11-08 SPEAR_Footprints: Add SPEAR logo silkscreen footprint
2025-11-09 Added symbol for motor driver board and started the schematic
2025-11-10 deleted incorrect file s
2025-11-10 Added corrected file
2025-11-14 Added Microcontroller symbol
2025-11-15 First draft of dev board
2025-11-15 Started Carrier Board PCB layout
2025-11-22 Renamed Spear lan9252 footprint library to have .pretty, and renamed to library naming standards.
2025-11-22 Changed folder address for LAN9252
2025-11-22 Changed it for real this time
2025-11-27 Update SPEAR_V1.kicad_sch
    added communication protocols, esd protection for usb, voltage regulator
2025-11-27 Merged
    merged LAN and EtherCAT
2025-11-29 added Carrier Board PCB
2025-12-04 Header pins, st-link and vcap
2025-12-13 Update SPEAR_V1.kicad_sch
    Footprints
2026-01-06 Update README.md
    Added instructions to set up the environment variable
2026-01-07 Updated Schematic and routing
2026-01-07 Chris editted this.
2026-01-07 changes to lan setting
2026-01-07 more
2026-01-10 Added Lan9252 EtherCAT system to the microcontroller dev board. The schematic is updated, but the pcb layout is still being worked on.
2026-01-10 moved board footprints and created new motor driver board footprints
2026-01-11 ST L4971 Buck Converter
2026-01-12 Continued work on the EtherCAT microcontroller dev. board. Not complete yet.
2026-01-13 Henry's continued work on the EtherCAT microcontroller dev. board.
2026-01-13 Continued work on the pcb layout of the EtherCAT uC dev board. Updated schematic to use a power mux.
2026-01-14 Edited schematic to fix problems with Lan9252. Continued work on pcb layout.
2026-01-14 AP63203 Buck Converter Finished
2026-01-16 Continued work on the PCB layout of the EtherCAT microcontroller dev board. Not complete yet.
2026-01-17 Continued work on EtherCAT microcontroller dev board. Updated it's head pinout.
2026-01-17 Created board symbols and added buck converter to carrier board
2026-01-17 PCB Power Junction
    This is the Power Junction PCB design
2026-01-17 Moved buck converter footprints to SPEAR_Footprints
2026-01-17 Started adding digikey part ID's to the EtherCAT microcontroller dev. board, but incomplete as of now.
2026-01-22 Finished etherCAT microcontroller dev board component selection. BOM is available. PCB layout incomplete.
2026-01-23 Finished schematic and general PCB layout for carrier board 2992
2026-01-24 Continued work on the Ethercat dev board. Unfinished.
2026-01-24 Added silkscreen and courtyards to board footprints and 3D models to the carrier board
2026-01-24 Started redesigning the carrier board to have the correct dimensions
2026-01-26 Finished version 1.0 of the EtherCAT STM32 Development Board. Gerber files (and drill files) are available.
2026-01-29 Moved power traces to the back for carrier board
2026-01-31 Moved power traces to the front and made minor adjustments to the layout of the carrier board
2026-01-31 updates to design
2026-02-01 Almost finished getting carrier board ready for fabrication
2026-02-04 Added board-to-board connectors to schematic and swapped out THT capacitors for SMT ones in carrier board
2026-02-05 Generated gerbers for carrier board with new buck converter layout
2026-02-05 Updated fabrications specs file for carrier board
2026-02-05 Made interactive html bom for ethercat microcontroller board.
2026-02-05 Updated interative html bom for ethercat microcontroller board to ignore DNP components.
2026-02-12 Updated Power junction design and fabrication folder
2026-02-14 updates to pcb power junction design
2026-02-20 Single Brushed DC Motor Drive Carrier PCB
2026-03-07 Duplicated EtherCatDevBoard_V1 pcb design to start a version 1.1.
2026-03-13 Routed traces for unconnected pins on stepper motor driver and did some organizing
2026-03-14 Moved mounting hole on stepper controller carrier
2026-03-20 Almost finished board
2026-03-21 Updates to V1.1 for Ecat dev board.
2026-04-20 Updated Junction board
2026-05-01 Finished the Ecat Dev Boar V1.1. Fabrication files are available.
2026-05-01 Made interactive html bom available for Ecat Dev Board V1.1.
2026-05-06 Updated Ecat dev board v1.1 to use vias with hole size 0.3mm and diameter 0.45mm to match jlcpcb. Also moved vias to avoid solder mask openings to prevent solder wicking.
2026-05-09 Updated Gerber files
2026-05-09 Changed ecat dev board v1.1 fabrication specifications to use 0.5oz inner copper weight, and the stencil is 150mm by 150mm now. The specifications file is a markdown file now.
2026-05-09 Added Fabrication Spec
2026-05-09 Added BOM for the Junction Board
2026-05-10 created gerbers for stepper controller board
2026-05-10 updated stepper controller board
2026-06-07 created BMS board schematic
